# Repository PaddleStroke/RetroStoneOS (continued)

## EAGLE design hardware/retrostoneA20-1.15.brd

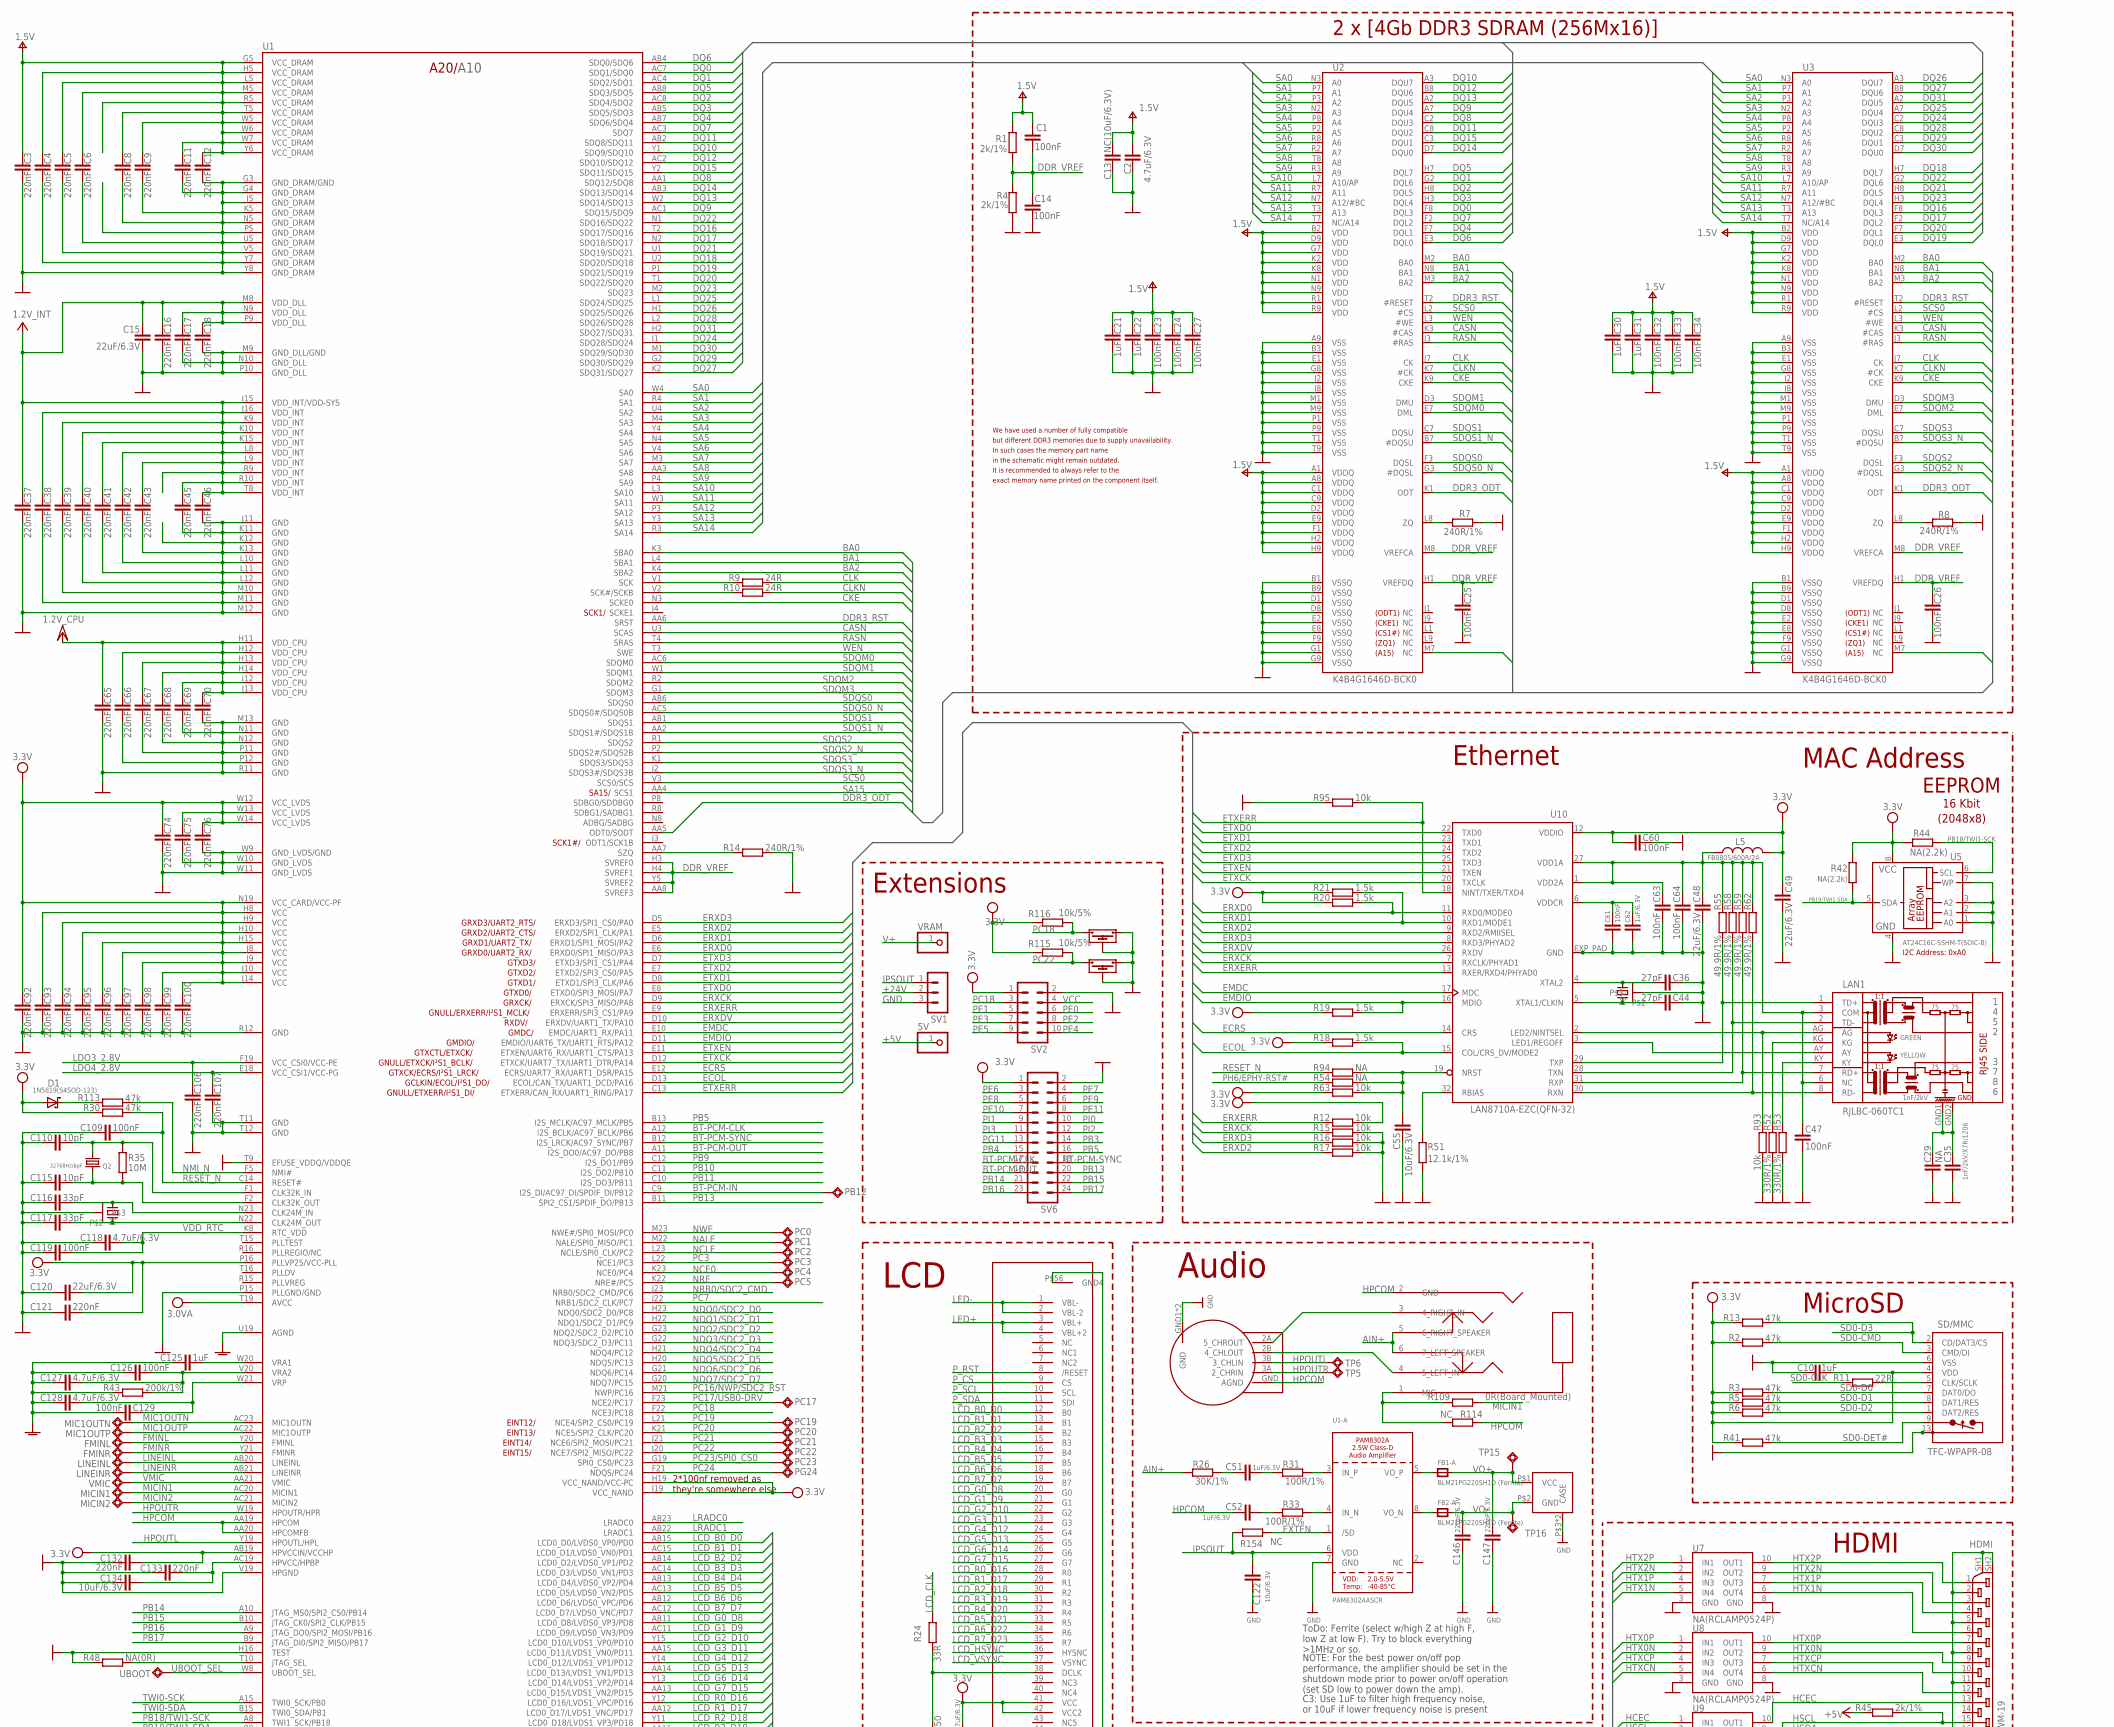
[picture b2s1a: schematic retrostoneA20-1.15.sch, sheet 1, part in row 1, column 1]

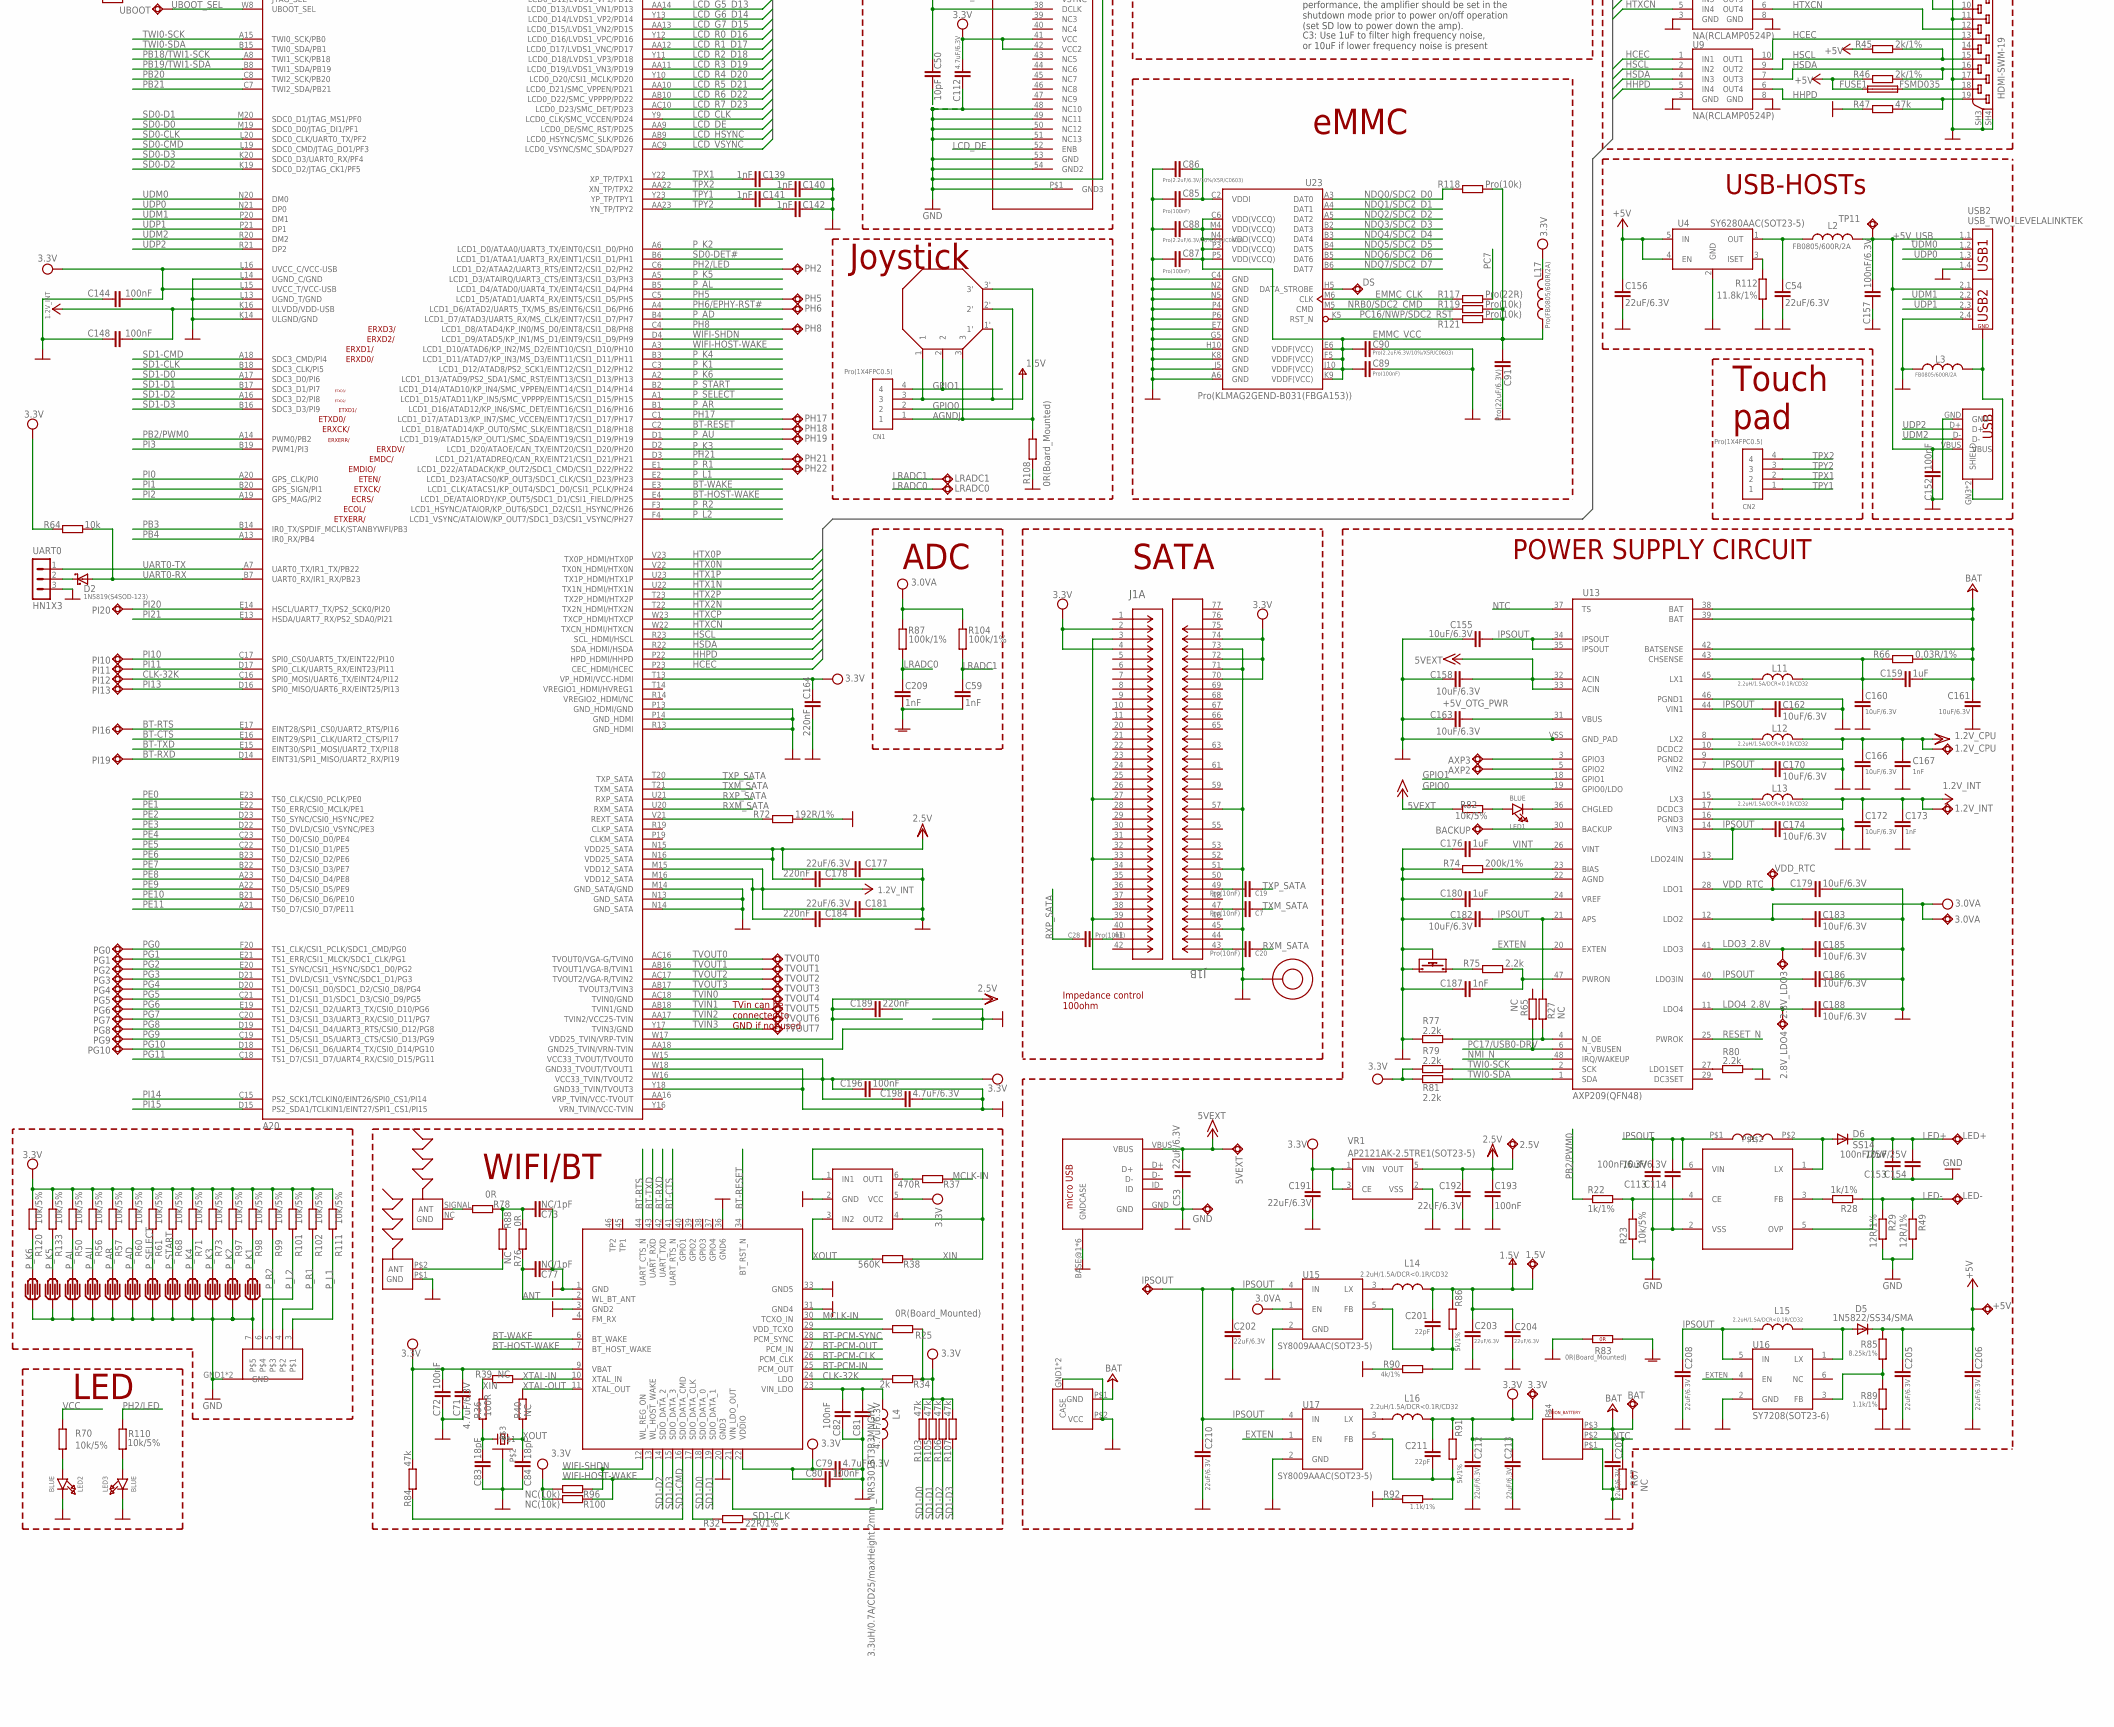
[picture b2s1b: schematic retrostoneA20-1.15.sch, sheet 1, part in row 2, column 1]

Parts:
1.2V_CPU, 1.2V_INT, 1.5V, 2.5V, 2.8V_LDO3, 2.8V_LDO4, 3.0VA, 3.3V, 5VEXT: TESTPADTESTPAD_40-ROUND; TESTPAD_40-ROUND
5V: PINHD-1X1; 1X01
+5V: TESTPADTESTPAD_40-ROUND; TESTPAD_40-ROUND
AXP2, AXP3: TESTPADTESTPAD30/30; TESTPAD_30-ROUND
BACKUP: TESTPADTESTPAD30/30; TESTPAD_30-ROUND
BAT: TESTPADTESTPAD_40-ROUND; TESTPAD_40-ROUND
C1, C14, C23, C24, C25, C26, C27, C32, C33, C34, C47, C60, C61, C63, C64, C72, C80, C82, C109, C119, C126, C129, C144, C148, C152, C193, C196: 100nF; C0402_TI
C2, C71, C79, C81, C112, C118, C127, C128, C198: 4.7uF/6.3V; C0603_DWS
C3, C4, C5, C6, C8, C9, C11, C12, C16, C17, C18, C37, C38, C39, C40, C41, C42, C43, C45, C46, C65, C66, C67, C68, C69, C70, C74, C75, C76, C92, C93, C94, C95, C96, C97, C98, C99, C100, C106, C107, C121, C132, C133, C164, C178, C184, C189: 220nF; C0402_TI
C7, C19, C20, C28: Pro(10nF); C0402_TI
C10, C21, C22, C30, C31, C125, C176, C180: 1uF; C0402_TI
C13: NC(10uF/6.3V); C0603_DWS
C15, C48, C49, C53, C54, C120, C156, C177, C181, C191, C192, C202, C203, C204, C205, C206, C207, C208, C210, C212, C213: 22uF/6.3V; C0603_DWS
C29: NA; C1206_5MILS_WS_ISO
C35: 1nF/2kV/X7R/1206; C1206_5MILS_WS_ISO
C36, C44: 27pF; C0402_TI
C50, C110, C115: 10pF; C0402_TI
C51, C52: 1uF/6.3V; C0402_TI
C55, C114, C122, C134, C155, C158, C160, C161, C162, C163, C166, C170, C172, C174, C179, C182, C183, C185, C186, C188: 10uF/6.3V; C0603_DWS
C59, C139, C140, C141, C142, C167, C173, C187, C209: 1nF; C0402_TI
C62: 1uF/6.3V; C0603_DWS
C73, C77: NC/1pF; C0402_TI
C83, C84: 18pF; C0402_TI
C85, C87, C89: Pro(100nF); C0402_TI
C86, C88, C90: Pro(2.2uF/6.3V/10%/X5R/C0603); C0603_DWS
C91: Pro(22uF/6.3V); C0603_DWS
C113, C157: 100nF/6.3V; C0402_TI
C116, C117: 33pF; C0402_TI
C146, C147: 220pF/6.3V; C0402_TI
C153: 100nF/25V; C0805_5MIL
C154: 10uF/25V; C0805_5MIL
C159: 1uF; C0603_DWS
C201, C211: 22pF; C0402_TI
CN1, CN2: Pro(1X4FPC0.5); FPC_0.5MM-4
D1, D2: 1N5819(S4SOD-123); SOD-123
D5: 1N5822/SS34/SMA; MELF-MLL41
D6: SS14; DO214AC
DOWN: PAD_BUTTON
DS: TESTPADTESTPAD_40-ROUND; TESTPAD_40-ROUND
FB1-A, FB2-A: BLM21PG220SH1D (Ferrite); _0805
FMINL: TESTPADTESTPAD_40-ROUND; TESTPAD_40-ROUND
FMINR: TESTPADTESTPAD_40-ROUND; TESTPAD_40-ROUND
FUSE1: FSMD035; 1206
GND: TESTPADTESTPAD_40-ROUND; TESTPAD_40-ROUND
HDMI: HDMI-SWM-19
IPSOUT: TESTPADTESTPAD_40-ROUND; TESTPAD_40-ROUND
J1: Pro(1-2199230-5-LITE); CONN67_2199230_LITE
K1, K2, K3, K4: PAD_BUTTON
L1: 22uH/CD32; CD32_INDUCTOR
L2, L3, L5: FB0805/600R/2A; L0805_5MIL_DWS
L4: 3.3uH/0.7A/CD25/maxHeight 2mm _NRS3015T3R3MNGHV; CD25
L11, L12, L13, L14, L15, L16: 2.2uH/1.5A/DCR<0.1R/CD32; CD32
L17: Pro(FB0805/600R/2A); L0805_5MIL_DWS
LAN1: RJLBC-060TC1; RJLBC-060TC1_MILLING
LED1, LED2, LED3: BLUE; CHIPLED_0805_NOOUTLINE
LED+: TESTPADTESTPAD_40-ROUND; TESTPAD_40-ROUND
LED-: TESTPADTESTPAD_40-ROUND; TESTPAD_40-ROUND
LEFT: PAD_BUTTON
LINEINL: TESTPADTESTPAD_40-ROUND; TESTPAD_40-ROUND
LINEINR: TESTPADTESTPAD_40-ROUND; TESTPAD_40-ROUND
LRADC0, LRADC1: TESTPADTESTPAD_40-ROUND; TESTPAD_40-ROUND
MIC1OUTN, MIC1OUTP: TESTPADTESTPAD_40-ROUND; TESTPAD_40-ROUND
MICIN1, MICIN2: TESTPADTESTPAD_40-ROUND; TESTPAD_40-ROUND
PB12: TESTPADTESTPAD_40-ROUND; TESTPAD_40-ROUND
PC0, PC1, PC2, PC3, PC4, PC5, PC17, PC19, PC20, PC21, PC22, PC23: TESTPADTESTPAD_40-ROUND; TESTPAD_40-ROUND
PG0, PG1, PG2, PG3, PG4, PG5, PG6, PG7, PG8, PG9, PG10, PG24: TESTPADTESTPAD_40-ROUND; TESTPAD_40-ROUND
PH2, PH5: TESTPADTESTPAD30/30; TESTPAD_30-ROUND
PH6, PH8, PH17, PH18, PH19, PH21, PH22: TESTPADTESTPAD_40-ROUND; TESTPAD_40-ROUND
PI10, PI11, PI12, PI13, PI16, PI19, PI20: TESTPADTESTPAD_40-ROUND; TESTPAD_40-ROUND
Q2: 32768Hz/6pF; MC-306
R1, R4, R45, R46: 2k/1%; R0402_TI
R2, R3, R5, R6, R13, R30, R41, R47, R84, R103, R105, R106, R107, R113: 47k; R0402_TI
R7, R8, R14: 240R/1%; R0402_TI
R9, R10: 24R; R0402_TI
R11: 22R; R0402_TI
R12, R15, R16, R17, R63, R64, R93, R95: 10k; R0402_TI
R18, R19, R20, R21: 1.5k; R0402_TI
R22, R28: 1k/1%; R0402_TI
R23, R50, R56, R57, R60, R61, R68, R70, R71, R73, R82, R97, R98, R99, R101, R102, R110, R111, R115, R116, R120, R133: 10k/5%; R0402_TI
R24: 33R; R0402_TI
R25, R108, R109: 0R(Board_Mounted); R0402_TI_0R
R26: 30K/1%; R0402_TI
R27, R39, R40, R65, R67, R88, R114, R154: NC; R0402_TI
R29, R49: 12R/1%; R0603_5MIL_DWS
R31, R33: 100R/1%; R0402_TI
R32: 22R/1%; R0402_TI
R34: 2k; R0402_TI
R35: 10M; R0402_TI
R36: 100R; R0402_TI
R37: 470R; R0402_TI
R38: 560K; R0402_TI
R42, R44: NA(2.2k); R0603_5MIL_DWS
R43, R74: 200k/1%; R0402_TI
R48: NA(0R); R0402_TI
R51: 12.1k/1%; R0402_TI
R52, R53: 330R/1%; R0603_5MIL_DWS
R54, R94: NA; R0402_TI
R55, R58, R59, R62: 49.9R/1%; R0402_TI
R66: 0.03R/1%; R1206_5MIL_WS
R72: 192R/1%; R0402_TI
R75, R77, R79, R80, R81: 2.2k; R0402_TI
R76, R78: 0R; R0402_TI
R83: 0R(Board_Mounted); 0603_0R
R85: 8.25k/1%; R0402_TI
R86, R91: 5k/1%; R0402_TI
R87, R104: 100k/1%; R0402_TI
R89, R92: 1.1k/1%; R0402_TI
R90: 4k/1%; R0402_TI
R96, R100: NC(10k); R0402_TI
R112: 11.8k/1%; R0402_TI
R117: Pro(22R); R0402_TI
R118, R119, R121: Pro(10k); R0402_TI
RIGHT: PAD_BUTTON
SD/MMC: TFC-WPAPR-08
SELECT, SELECT3, SELECT4: PAD_BUTTON
START: PAD_BUTTON
SV1: MA03-1
SV2: MA05-2
SV6: MA12-2
TP5, TP6, TP11, TP15, TP16: TESTPADTESTPAD_40-ROUND; TESTPAD_40-ROUND
TVOUT0, TVOUT2, TVOUT3: TESTPADTESTPAD_40-ROUND; TESTPAD_40-ROUND
TVOUT1, TVOUT4, TVOUT5, TVOUT6, TVOUT7: TESTPADTESTPAD30/30; TESTPAD_30-ROUND
U1: A20; TFBGA441
U1-A: PAM8302AASCR; MSOP8_0.65MM
U2, U3: K4B4G1646D-BCK0; FBGA96_SK
U4: SY6280AAC(SOT23-5); SOT23-5
U5: AT24C16C-SSHM-T(SOIC-8); SO-08MN
U7, U8, U9: NA(RCLAMP0524P); SLP2510P8
U10: LAN8710A-EZC(QFN-32); QFN-32(DRILLS)
U13: AXP209(QFN48); QFN48
U14: KA2707; SOT23-6
U15, U17: SY8009AAAC(SOT23-5); SOT23-5
U16: SY7208(SOT23-6); SOT23-6
U23: Pro(KLMAG2GEND-B031(FBGA153)); FBGA153
U$1: USB_HAYATO; USBA_HAYATO
U$2: AP6210; AP6212
U$3: 26MHZ_12pF; TSX-3225
U$4: JST_PH_VERT_5P
U$5, U$31, U$32: TACT_SWITCH_HORIZONTAL
U$6: NC(JST_PH_VERT_2P); JST_PH_VERT_2P
U$7: FPC_HAYATO
U$8: ESP8089_ANTSYM; ANT_ESP8206_SYM
U$15: JST2_HAYATO1.25_HOR_2PIN; JST1.25_HOR_2P
U$17: MICROUSB_HAYATO
U$18: BC-75-3PD700(750-800); BATTERY_CON_3PIN
U$20: SCREW_M2_04
U$21: 24MHz/20ppm/20pF; TSX-3225
U$23: 25MHZ/20pF/20ppm; TSX-3225
U$24: PJ342_5PIN; PJ342_6P
U$27: WHEEL_POT
U$29: NL27WZU04; SOT23-6
U$30: ANT_H2U262GKBA0100
U$33: JOYSTICK-POT
UART0: HN1X3
UBOOT: TESTPADTESTPAD_40-ROUND; TESTPAD_40-ROUND
UP: PAD_BUTTON
USB2: USB_TWO_LEVELALINKTEK; USB_TWO_LEVEL_ALINKTEK
VDD_RTC: TESTPADTESTPAD_40-ROUND; TESTPAD_40-ROUND
VMIC: TESTPADTESTPAD_40-ROUND; TESTPAD_40-ROUND
VR1: AP2121AK-2.5TRE1(SOT23-5); SOT-23-5
VRAM: PINHD-1X1; 1X01

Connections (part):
5VEXT: 5VEXT.1, C53.2, C158.2, R82.1, U13.32 (ACIN), U13.33 (ACIN), U$17.VBUS
+5V: 5V.1, +5V.1, C156.1, C205.1, C206.1, D5.1 (C), FUSE1.1, R45.2, R46.2, R85.2, U4.4 (EN), U4.5 (IN)
+5V_OTG_PWR: C163.2, U13.31 (VBUS)
+5V_USB: C152.1, C157.1, L2.1, TP11.1, U$1.VBUS, USB2.1.1, USB2.2.1
+24V: BAT.1, C159.2, C161.1, C207.2, R66.2, SV1.2, U13.38 (BAT), U13.39 (BAT), U13.42 (BATSENSE), U$6.P$1 (GND), U$18.P$3
AGNDJ: CN1.1, R108.1, U$33.3, U$33.3'
AIN+: R26.1, U$24.5 (6_RIGHT_SPEAKER), U$24.6 (7_LEFT_SPEAKER)
ANT: C77.2, R76.1, U$2.2 (WL_BT_ANT)
BA0: U1.K3 (SBA0), U2.M2 (BA0), U3.M2 (BA0)
BA1: U1.L4 (SBA1), U2.N8 (BA1), U3.N8 (BA1)
BA2: U1.K4 (SBA2), U2.M3 (BA2), U3.M3 (BA2)
BT-CTS: U1.E16 (EINT29/SPI1_CLK/UART2_CTS/PI17), U$2.41 (UART_RTS_N)
BT-HOST-WAKE: U1.E4 (LCD1_DE/ATAIORDY/KP_OUT5/SDC1_D1/CSI1_F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), U$2.7 (BT_HOST_WAKE)
BT-PCM-CLK: SV6.17, U1.A12 (I2S_BCLK/AC97_BCLK/PB6), U$2.26 (PCM_CLK)
BT-PCM-IN: PB12.1, U1.C9 (I2S_DI/AC97_DI/SPDIF_DI/PB12), U$2.25 (PCM_OUT)
BT-PCM-OUT: SV6.19, U1.A11 (I2S_DO0/AC97_DO/PB8), U$2.27 (PCM_IN)
BT-PCM-SYNC: SV6.18, U1.B12 (I2S_LRCK/AC97_SYNC/PB7), U$2.28 (PCM_SYNC)
BT-RESET: PH18.1, U1.C2 (LCD1_D18/ATAD14/KP_OUT0/SMC_SLK/EINT18/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), U$2.34 (BT_RST_N)
BT-RTS: PI16.1, U1.E17 (EINT28/SPI1_CS0/UART2_RTS/PI16), U$2.44 (UART_CTS_N)
BT-RXD: PI19.1, U1.D14 (EINT31/SPI1_MISO/UART2_RX/PI19), U$2.42 (UART_TXD)
BT-TXD: U1.E15 (EINT30/SPI1_MOSI/UART2_TX/PI18), U$2.43 (UART_RXD)
BT-WAKE: U1.E3 (LCD1_CLK/ATACS1/KP_OUT4/SDC1_D0/CSI1_PC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), U$2.6 (BT_WAKE)
CASN: U1.U3 (SCAS), U2.K3 (#CAS), U3.K3 (#CAS)
CHASSIS: C29.2, C35.2, LAN1.GND1, LAN1.GND2
CKE: U1.N3 (SCKE0), U2.K9 (CKE), U3.K9 (CKE)
CLK: R9.1, U2.J7 (CK), U3.J7 (CK)
CLK-32K: PI12.1, R34.1, U1.C16 (SPI0_MOSI/UART6_TX/EINT24/PI12), U$2.24 (LDO)
CLKN: R10.1, U2.K7 (#CK), U3.K7 (#CK)
DDR3_ODT: U1.AA5 (ODT0/SODT), U2.K1 (ODT), U3.K1 (ODT)
DDR3_RST: U1.AA6 (SRST), U2.T2 (#RESET), U3.T2 (#RESET)
DDR_VREF: C1.2, C14.2, C25.2, C26.2, R1.1, R4.2, U1.AA8 (SVREF3), U1.H3 (SVREF0), U1.H4 (SVREF1), U1.Y5 (SVREF2), U2.H1 (VREFDQ), U2.M8 (VREFCA), U3.H1 (VREFDQ), U3.M8 (VREFCA)
DQ0: U1.AC7 (SDQ1/SDQ0), U2.F8 (DQL3)
DQ1: U1.AC4 (SDQ2/SDQ1), U2.G2 (DQL6)
DQ2: U1.AC8 (SDQ4/SDQ2), U2.H8 (DQL5)
DQ3: U1.AB5 (SDQ5/SDQ3), U2.H3 (DQL4)
DQ4: U1.AB7 (SDQ6/SDQ4), U2.F7 (DQL1)
DQ5: U1.AB8 (SDQ3/SDQ5), U2.H7 (DQL7)
DQ6: U1.AB4 (SDQ0/SDQ6), U2.E3 (DQL0)
DQ7: U1.AC3 (SDQ7), U2.F2 (DQL2)
DQ8: U1.AA1 (SDQ12/SDQ8), U2.C2 (DQU3)
DQ9: U1.AC1 (SDQ15/SDQ9), U2.A7 (DQU4)
DQ10: U1.Y1 (SDQ9/SDQ10), U2.A3 (DQU7)
DQ11: U1.AB2 (SDQ8/SDQ11), U2.C8 (DQU2)
DQ12: U1.AC2 (SDQ10/SDQ12), U2.B8 (DQU6)
DQ13: U1.W2 (SDQ14/SDQ13), U2.A2 (DQU5)
DQ14: U1.AB3 (SDQ13/SDQ14), U2.D7 (DQU0)
DQ15: U1.Y2 (SDQ11/SDQ15), U2.C3 (DQU1)
DQ16: U1.T2 (SDQ17/SDQ16), U3.F8 (DQL3)
DQ17: U1.N2 (SDQ18/SDQ17), U3.F2 (DQL2)
DQ18: U1.U2 (SDQ20/SDQ18), U3.H7 (DQL7)
DQ19: U1.P1 (SDQ21/SDQ19), U3.E3 (DQL0)
DQ20: U1.T1 (SDQ22/SDQ20), U3.F7 (DQL1)
DQ21: U1.U1 (SDQ19/SDQ21), U3.H8 (DQL5)
DQ22: U1.N1 (SDQ16/SDQ22), U3.G2 (DQL6)
DQ23: U1.M2 (SDQ23), U3.H3 (DQL4)
DQ24: U1.J1 (SDQ28/SDQ24), U3.C2 (DQU3)
DQ25: U1.L1 (SDQ24/SDQ25), U3.A7 (DQU4)
DQ26: U1.H1 (SDQ25/SDQ26), U3.A3 (DQU7)
DQ27: U1.K2 (SDQ31/SDQ27), U3.B8 (DQU6)
DQ28: U1.L2 (SDQ26/SDQ28), U3.C8 (DQU2)
DQ29: U1.G2 (SDQ30/SDQ29), U3.C3 (DQU1)
DQ30: U1.M1 (SDQ29/SQD30), U3.D7 (DQU0)
DQ31: U1.H2 (SDQ27/SDQ31), U3.A2 (DQU5)
ECOL: R18.2, U1.D13 (ECOL/CAN_TX/UART1_DCD/PA16), U10.15 (COL/CRS_DV/MODE2)
ECRS: U1.E12 (ECRS/UART7_RX/UART1_DSR/PA15), U10.14 (CRS)
EMDC: U1.E10 (EMDC/UART1_RX/PA11), U10.17 (MDC)
EMDIO: R19.2, U1.D11 (EMDIO/UART6_TX/UART1_RTS/PA12), U10.16 (MDIO)
EMMC_CLK: R117.2, U23.M6 (CLK)
EMMC_VCC: C87.1, C88.2, C89.1, C90.2, C91.1, L17.2, R118.1, R119.1, R121.1, U23.C6 (VDD(VCCQ)), U23.E6 (VDDF(VCC)), U23.F5 (VDDF(VCC)), U23.J10 (VDDF(VCC)), U23.K9 (VDDF(VCC)), U23.M4 (VDD(VCCQ)), U23.N4 (VDD(VCCQ)), U23.P3 (VDD(VCCQ)), U23.P5 (VDD(VCCQ))
ERXCK: R15.1, U1.D9 (ERXCK/SPI3_MISO/PA8), U10.7 (RXCLK/PHYAD1)
ERXD0: R20.2, U1.E6 (ERXD0/SPI1_MISO/PA3), U10.11 (RXD0/MODE0)
ERXD1: R21.2, U1.D6 (ERXD1/SPI1_MOSI/PA2), U10.10 (RXD1/MODE1)
ERXD2: R17.1, U1.E5 (ERXD2/SPI1_CLK/PA1), U10.9 (RXD2/RMIISEL)
ERXD3: R16.1, U1.D5 (ERXD3/SPI1_CS0/PA0), U10.8 (RXD3/PHYAD2)
ERXDV: U1.D10 (ERXDV/UART1_TX/PA10), U10.26 (RXDV)
ERXERR: R12.1, U1.E9 (ERXERR/SPI3_CS1/PA9), U10.13 (RXER/RXD4/PHYAD0)
ETHERNET_VDD: C47.2, C48.2, C63.2, C64.2, L5.1, LAN1.3 (COM), LAN1.6 (NC), R55.2, R58.2, R59.2, R62.2, U10.1 (VDD2A), U10.27 (VDD1A)
ETXCK: U1.D12 (ETXCK/UART7_TX/UART1_DTR/PA14), U10.20 (TXCLK)
ETXD0: U1.E8 (ETXD0/SPI3_MOSI/PA7), U10.22 (TXD0)
ETXD1: U1.D8 (ETXD1/SPI3_CLK/PA6), U10.23 (TXD1)
ETXD2: U1.E7 (ETXD2/SPI3_CS0/PA5), U10.24 (TXD2)
ETXD3: U1.D7 (ETXD3/SPI1_CS1/PA4), U10.25 (TXD3)
ETXEN: U1.E11 (ETXEN/UART6_RX/UART1_CTS/PA13), U10.21 (TXEN)
ETXERR: R95.2, U1.C13 (ETXERR/CAN_RX/UART1_RING/PA17), U10.18 (NINT/TXER/TXD4)
EXTEN: R154.2, U1-A.1 (/SD), U13.20 (EXTEN), U16.4 (EN), U17.1 (EN)
FMINL: FMINL.1, U1.Y20 (FMINL)
FMINR: FMINR.1, U1.Y21 (FMINR)
GND: C2.1, C3.1, C4.1, C5.1, C6.1, C8.1, C9.1, C10.2, C11.1, C12.1, C13.1, C14.1, C15.1, C16.1, C17.1, C18.1, C21.1, C22.1, C23.1, C24.1, C25.1, C26.1, C27.1, C29.1, C30.1, C31.1, C32.1, C33.1, C34.1, C35.1, C36.1, C37.1, C38.1, C39.1, C40.1, C41.1, C42.1, C43.1, C44.1, C45.1, C46.1, C47.1, C48.1, C49.1, C50.2, C53.1, C54.2, C55.1, C60.1, C61.1, C62.1, C63.1, C64.1, C65.1, C66.1, C67.1, C68.1, C69.1, C70.1, C71.2, C72.1, C73.1, C74.1, C75.1, C76.1, C77.1, C79.1, C80.2, C81.2, C82.1, C83.1, C84.1, C85.2, C86.1, C87.2, C88.1, C89.2, C90.1, C91.2, C92.1, C93.1, C94.1, C95.1, C96.1, C97.1, C98.1, C99.1, C100.1, C106.1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
GNDA: C59.2, C125.1, C126.1, C127.1, C128.1, C129.1, C209.2, R43.2, R83.2 (1.2), U1.U19 (AGND)
GPIO0: CN1.2, U13.19 (GPIO0/LDO), U$33.2'
GPIO1: CN1.4, U13.18 (GPIO1), U$33.2
HCEC: HDMI.13, U1.P23 (CEC_HDMI/HCEC), U9.1 (IN1), U9.10 (OUT1)
HDMI_5V_SOURCE: FUSE1.2, HDMI.18
HHPD: HDMI.19, R47.1, U1.P22 (HPD_HDMI/HHPD), U9.5 (IN4), U9.6 (OUT4)
HPCOM: C52.1, R114.1, U1.AA19 (HPCOM), U1.AA20 (HPCOMFB), U$24.2 (GND), U$27.GND (AGND)
HPOUTL: TP6.1, U1.Y19 (HPOUTL/HPL), U$27.3B (3_CHLIN)
HPOUTR: TP5.1, U1.W19 (HPOUTR/HPR), U$27.3A (2_CHRIN)
HSCL: HDMI.15, R45.1, U1.R23 (SCL_HDMI/HSCL), U9.2 (IN2), U9.9 (OUT2)
HSDA: HDMI.16, R46.1, U1.R22 (SDA_HDMI/HSDA), U9.4 (IN3), U9.7 (OUT3)
HTX0N: HDMI.9, U1.V22 (TX0N_HDMI/HTX0N), U8.2 (IN2), U8.9 (OUT2)
HTX0P: HDMI.7, U1.V23 (TX0P_HDMI/HTX0P), U8.1 (IN1), U8.10 (OUT1)
HTX1N: HDMI.6, U1.U22 (TX1N_HDMI/HTX1N), U7.5 (IN4), U7.6 (OUT4)
HTX1P: HDMI.4, U1.U23 (TX1P_HDMI/HTX1P), U7.4 (IN3), U7.7 (OUT3)
HTX2N: HDMI.3, U1.T22 (TX2N_HDMI/HTX2N), U7.2 (IN2), U7.9 (OUT2)
HTX2P: HDMI.1, U1.T23 (TX2P_HDMI/HTX2P), U7.1 (IN1), U7.10 (OUT1)
HTXCN: HDMI.12, U1.W22 (TXCN_HDMI/HTXCN), U8.5 (IN4), U8.6 (OUT4)
HTXCP: HDMI.10, U1.W23 (TXCP_HDMI/HTXCP), U8.4 (IN3), U8.7 (OUT3)
IPSOUT: C113.2, C114.2, C122.2, C155.2, C162.1, C170.1, C174.1, C182.2, C186.1, C202.1, C208.2, C210.1, IPSOUT.1, L1.P$1, L15.1, R27.1, R154.1, SV1.1, U1-A.6 (VDD), U13.7 (VIN2), U13.13 (LDO24IN), U13.14 (VIN3), U13.21 (APS), U13.34 (IPSOUT), U13.35 (IPSOUT), U13.40 (LDO3IN), U13.44 (VIN1), U14.6 (VIN), U15.4 (IN), U16.5 (IN), U17.4 (IN)
LCD_B0_D0: U1.AB15 (LCD0_D0/LVDS0_VP0/PD0), U$7.12 (B0)
LCD_B1_D1: U1.AC15 (LCD0_D1/LVDS0_VN0/PD1), U$7.13 (B1)
LCD_B2_D2: U1.AB14 (LCD0_D2/LVDS0_VP1/PD2), U$7.14 (B2)
LCD_B3_D3: U1.AC14 (LCD0_D3/LVDS0_VN1/PD3), U$7.15 (B3)
LCD_B4_D4: U1.AB13 (LCD0_D4/LVDS0_VP2/PD4), U$7.16 (B4)
LCD_B5_D5: U1.AC13 (LCD0_D5/LVDS0_VN2/PD5), U$7.17 (B5)
LCD_B6_D6: U1.AB12 (LCD0_D6/LVDS0_VPC/PD6), U$7.18 (B6)
LCD_B7_D7: U1.AC12 (LCD0_D7/LVDS0_VNC/PD7), U$7.19 (B7)
LCD_CLK: R24.2, U1.Y9 (LCD0_CLK/SMC_VCCEN/PD24)
LCD_DE: U1.AA9 (LCD0_DE/SMC_RST/PD25), U$7.52 (ENB)
LCD_G0_D8: U1.AB11 (LCD0_D8/LVDS0_VP3/PD8), U$7.20 (G0)
LCD_G1_D9: U1.AC11 (LCD0_D9/LVDS0_VN3/PD9), U$7.21 (G1)
LCD_G2_D10: U1.Y15 (LCD0_D10/LVDS1_VP0/PD10), U$7.22 (G2)
LCD_G3_D11: U1.AA15 (LCD0_D11/LVDS1_VN0/PD11), U$7.23 (G3)
LCD_G4_D12: U1.Y14 (LCD0_D12/LVDS1_VP1/PD12), U$7.24 (G4)
LCD_G5_D13: U1.AA14 (LCD0_D13/LVDS1_VN1/PD13), U$7.25 (G5)
LCD_G6_D14: U1.Y13 (LCD0_D14/LVDS1_VP2/PD14), U$7.26 (G6)
LCD_G7_D15: U1.AA13 (LCD0_D15/LVDS1_VN2/PD15), U$7.27 (G7)
LCD_HSYNC: U1.AB9 (LCD0_HSYNC/SMC_SLK/PD26), U$7.36 (HYSNC)
LCD_R0_D16: U1.Y12 (LCD0_D16/LVDS1_VPC/PD16), U$7.28 (R0)
LCD_R1_D17: U1.AA12 (LCD0_D17/LVDS1_VNC/PD17), U$7.29 (R1)
LCD_R2_D18: U1.Y11 (LCD0_D18/LVDS1_VP3/PD18), U$7.30 (R2)
LCD_R3_D19: U1.AA11 (LCD0_D19/LVDS1_VN3/PD19), U$7.31 (R3)
LCD_R4_D20: U1.Y10 (LCD0_D20/CSI1_MCLK/PD20), U$7.32 (R4)
LCD_R5_D21: U1.AA10 (LCD0_D21/SMC_VPPEN/PD21), U$7.33 (R5)
LCD_R6_D22: U1.AB10 (LCD0_D22/SMC_VPPPP/PD22), U$7.34 (R6)
LCD_R7_D23: U1.AC10 (LCD0_D23/SMC_DET/PD23), U$7.35 (R7)
LCD_VSYNC: U1.AC9 (LCD0_VSYNC/SMC_SDA/PD27), U$7.37 (VSYNC)
LDO3_2.8V: 2.8V_LDO3.1, C106.2, C185.1, U1.F19 (VCC_CSI0/VCC-PE), U13.41 (LDO3)
LDO4_2.8V: 2.8V_LDO4.1, C107.2, C188.1, U1.E18 (VCC_CSI1/VCC-PG), U13.11 (LDO4)
LED+: C153.2, C154.2, D6.C, LED+.1, U14.5 (OVP), U$7.3 (VBL+), U$7.4 (VBL+2)
LED-: LED-.1, R28.1, R29.1, R49.1, U$7.1 (VBL-), U$7.2 (VBL-2)
LINEINL: LINEINL.1, U1.AB20 (LINEINL)
LINEINR: LINEINR.1, U1.AB21 (LINEINR)
LR: U$24.3 (4_RIGHT_IN), U$27.2A (5_CHROUT)
LRADC0: C209.1, LRADC0.1, R87.2, U1.AB23 (LRADC0)
LRADC1: C59.1, LRADC1.1, R104.2, U1.AB22 (LRADC1)
MCLK-IN: R37.2, U$2.30 (TCXO_IN)
MIC1OUTN: MIC1OUTN.1, U1.AC23 (MIC1OUTN)
MIC1OUTP: MIC1OUTP.1, U1.AC22 (MIC1OUTP)
MICIN1: MICIN1.1, R109.2, U1.AC20 (MICIN1)
MICIN2: MICIN2.1, U1.AC21 (MICIN2)
unnamed: C133.2, C134.2, U1.AC19 (HPVCC/HPBP)
unnamed: R14.2, U1.AA7 (SZQ)
unnamed: R7.2, U2.L8 (ZQ)
unnamed: LED2.A, R70.2
unnamed: R22.2, R23.2, U14.4 (CE)
unnamed: D6.A, L1.P$2, U14.1 (LX)
unnamed: D2.C, UART0.2
unnamed: L14.1, U15.3 (LX)
unnamed: R109.1, R114.2, U$24.1 (MIC)
unnamed: D1.C, R113.2
unnamed: LED1.C, U13.36 (CHGLED)
unnamed: R80.1, U13.27 (LDO1SET)
unnamed: C83.2, R36.2, U$3.P$1
unnamed: C110.2, Q2.4 (2), R35.1, U1.F1 (CLK32K_IN)
unnamed: R8.2, U3.L8 (ZQ)
unnamed: C50.1, R24.1, U$7.38 (DCLK)
unnamed: R28.2, U14.3 (FB)
unnamed: R112.2, U4.3 (ISET)
unnamed: C201.2, R86.2, R90.1, U15.5 (FB)
unnamed: C28.2, J1.41
unnamed: R75.1, U$5.P$2
unnamed: C20.2, J1.43
unnamed: R32.1, U$2.17 (SDIO_DATA_CLK)
unnamed: C54.1, L2.2, U4.1 (OUT)
unnamed: C7.2, J1.47
unnamed: C19.2, J1.49
unnamed: C73.2, R76.2, R78.1, R88.1
unnamed: L4.2, U$2.21 (VIN_LDO_OUT)
unnamed: C81.1, C82.2, L4.1, U$2.23 (VIN_LDO)
unnamed: BACKUP.1, U13.30 (BACKUP)
unnamed: R37.1, U$29.6 (OUT1)
unnamed: R88.2, U$8.P$2 (ANT)
unnamed: R78.2, U$30.SIGNAL (ANT)
unnamed: AXP2.1, U13.5 (GPIO2)
unnamed: DS.1, U23.H5 (DATA_STROBE)
unnamed: AXP3.1, U13.3 (GPIO3)
unnamed: R25.1, U$2.29 (VDD_TCXO)
unnamed: LED1.A, R82.2
unnamed: LED3.A, R110.2
unnamed: C51.1, R26.2
unnamed: L16.1, U17.3 (LX)
unnamed: C211.2, R91.2, R92.1, U17.5 (FB)
unnamed: R33.2, U1-A.4 (IN_N)
unnamed: R31.2, U1-A.3 (IN_P)
unnamed: C52.2, R33.1
unnamed: FB2-A.1, U1-A.8 (VO_N)
unnamed: FB1-A.1, U1-A.5 (VO_P)
unnamed: C51.2, R31.1
unnamed: U$24.4 (5_LEFT_IN), U$27.2B (4_CHLOUT)
unnamed: LAN1.1 (TD+), R55.1, U10.29 (TXP)
unnamed: LAN1.2 (TD-), R58.1, U10.28 (TXN)
unnamed: LAN1.7 (RD+), R59.1, U10.31 (RXP)
unnamed: LAN1.8 (RD-), R62.1, U10.30 (RXN)
unnamed: LAN1.AY, U10.3 (LED1/REGOFF)
unnamed: LAN1.AG, R93.1, U10.2 (LED2/NINTSEL)
unnamed: LAN1.KY, R53.1
unnamed: R51.2, U10.32 (RBIAS)
unnamed: C61.2, C62.2, U10.6 (VDDCR)
unnamed: LAN1.KG, R52.1
unnamed: C115.2, Q2.1, R35.2, U1.F2 (CLK32K_OUT)
unnamed: R72.2, U1.V21 (REXT_SATA)
unnamed: R74.2, U13.23 (BIAS)
unnamed: C128.2, C129.2, U1.W21 (VRP)
unnamed: D5.2 (A), L15.2, U16.1 (LX)
unnamed: R85.1, R89.1, U16.3 (FB)
unnamed: L11.1, U13.45 (LX1)
unnamed: C159.1, C160.1, L11.2, R66.1, U13.43 (CHSENSE)
unnamed: L12.1, U13.8 (LX2)
unnamed: L13.1, U13.15 (LX3)
unnamed: C180.2, U13.24 (VREF)
unnamed: C125.2, U1.W20 (VRA1)
unnamed: C187.2, R75.2, U13.47 (PWRON)
unnamed: R27.2, R77.2, U13.4 (N_OE)
unnamed: C126.2, C127.2, R43.1, U1.V20 (VRA2)
unnamed: R48.1, U1.T10 (JTAG_SEL)
unnamed: L3.2, U$1.GN3 (SHIELD), U$1.GND2 (SHIELD), USB2.GND1, USB2.GND2 (GND1), USB2.GND3 (GND1), USB2.GND4 (GND1)
NALE: PC1.1, U1.M22 (NALE/SPI0_MISO/PC1)
NCE0: PC4.1, U1.K23 (NCE0/PC4)
NCLE: PC2.1, U1.L23 (NCLE/SPI0_CLK/PC2)
NDQ0/SDC2_D0: R118.2, U1.H23 (NDQ0/SDC2_D0/PC8), U23.A3 (DAT0)
NDQ1/SDC2_D1: U1.H22 (NDQ1/SDC2_D1/PC9), U23.A4 (DAT1)
NDQ2/SDC2_D2: U1.G23 (NDQ2/SDC2_D2/PC10), U23.A5 (DAT2)
NDQ3/SDC2_D3: U1.G22 (NDQ3/SDC2_D3/PC11), U23.B2 (DAT3)
NDQ4/SDC2_D4: U1.H21 (NDQ4/PC12), U23.B3 (DAT4)
NDQ5/SDC2_D5: U1.H20 (NDQ5/PC13), U23.B4 (DAT5)
NDQ6/SDC2_D6: U1.G21 (NDQ6/PC14), U23.B5 (DAT6)
NDQ7/SDC2_D7: U1.G20 (NDQ7/PC15), U23.B6 (DAT7)
NMI_N: R113.1, U1.F5 (NMI#), U13.48 (IRQ/WAKEUP)
NRB0/SDC2_CMD: R119.2, U1.J23 (NRB0/SDC2_CMD/PC6), U23.M5 (CMD)
NRE: PC5.1, U1.K22 (NRE#/PC5)
NRST: C55.2, R54.2, R63.2, R94.2, U10.19 (NRST)
NTC: R67.1, U13.37 (TS), U$18.P$2
NWE: PC0.1, U1.M23 (NWE#/SPI0_MOSI/PC0)
PB2/PWM0: R22.1, U1.A14 (PWM0/PB2)
PB3: SV6.14, U1.B14 (IR0_TX/SPDIF_MCLK/STANBYWFI/PB3)
PB4: SV6.15, U1.A13 (IR0_RX/PB4)
PB5: SV6.16, U1.B13 (I2S_MCLK/AC97_MCLK/PB5)
PB9: U1.C12 (I2S_DO1/PB9)
PB10: U1.C11 (I2S_DO2/PB10)
PB11: U1.C10 (I2S_DO3/PB11)
PB13: SV6.20, U1.B11 (SPI2_CS1/SPDIF_DO/PB13)
PB14: SV6.21, U1.A10 (JTAG_MS0/SPI2_CS0/PB14)
PB15: SV6.22, U1.B10 (JTAG_CK0/SPI2_CLK/PB15)
PB16: SV6.23, U1.A9 (JTAG_DO0/SPI2_MOSI/PB16)
PB17: SV6.24, U1.B9 (JTAG_DI0/SPI2_MISO/PB17)
PB18/TWI1-SCK: R44.2, U1.A8 (TWI1_SCK/PB18), U5.6 (SCL)
PB19/TWI1-SDA: R42.1, U1.B8 (TWI1_SDA/PB19), U5.5 (SDA)
PB20: U1.C8 (TWI2_SCK/PB20)
PB21: U1.C7 (TWI2_SDA/PB21)
PC3: PC3.1, U1.L22 (NCE1/PC3)
PC7: R117.1, U1.J22 (NRB1/SDC2_CLK/PC7)
PC16/NWP/SDC2_RST: R121.2, U1.M21 (NWP/PC16), U23.K5 (RST_N)
PC17/USB0-DRV: PC17.1, R65.2, U1.F23 (NCE2/PC17), U13.6 (N_VBUSEN)
PC18: R116.2, SV2.3, U1.F22 (NCE3/PC18), U$32.P$3
PC19: PC19.1, U1.L21 (NCE4/SPI2_CS0/PC19)
PC20: PC20.1, U1.K21 (NCE5/SPI2_CLK/PC20)
PC21: PC21.1, U1.J21 (NCE6/SPI2_MOSI/PC21)
PC22: PC22.1, R115.2, U1.J20 (NCE7/SPI2_MISO/PC22), U$31.P$3
PC23/SPI0_CS0: PC23.1, U1.G19 (SPI0_CS0/PC23)
PC24: PG24.1, U1.F21 (NDQS/PC24)
PE0: SV2.6, U1.E23 (TS0_CLK/CSI0_PCLK/PE0)
PE1: SV2.5, U1.E22 (TS0_ERR/CSI0_MCLK/PE1)
PE2: SV2.8, U1.D23 (TS0_SYNC/CSI0_HSYNC/PE2)
PE3: SV2.7, U1.D22 (TS0_DVLD/CSI0_VSYNC/PE3)
PE4: SV2.10, U1.C23 (TS0_D0/CSI0_D0/PE4)
PE5: SV2.9, U1.C22 (TS0_D1/CSI0_D1/PE5)
PE6: SV6.3, U1.B23 (TS0_D2/CSI0_D2/PE6)
PE7: SV6.4, U1.B22 (TS0_D3/CSI0_D3/PE7)
PE8: SV6.5, U1.A23 (TS0_D4/CSI0_D4/PE8)
PE9: SV6.6, U1.A22 (TS0_D5/CSI0_D5/PE9)
PE10: SV6.7, U1.B21 (TS0_D6/CSI0_D6/PE10)
PE11: SV6.8, U1.A21 (TS0_D7/CSI0_D7/PE11)
PG0: PG0.1, U1.F20 (TS1_CLK/CSI1_PCLK/SDC1_CMD/PG0)
PG1: PG1.1, U1.E21 (TS1_ERR/CSI1_MLCK/SDC1_CLK/PG1)
PG2: PG2.1, U1.E20 (TS1_SYNC/CSI1_HSYNC/SDC1_D0/PG2)
PG3: PG3.1, U1.D21 (TS1_DVLD/CSI1_VSYNC/SDC1_D1/PG3)
PG4: PG4.1, U1.D20 (TS1_D0/CSI1_D0/SDC1_D2/CSI0_D8/PG4)
PG5: PG5.1, U1.C21 (TS1_D1/CSI1_D1/SDC1_D3/CSI0_D9/PG5)
PG6: PG6.1, U1.E19 (TS1_D2/CSI1_D2/UART3_TX/CSI0_D10/PG6)
PG7: PG7.1, U1.C20 (TS1_D3/CSI1_D3/UART3_RX/CSI0_D11/PG7)
PG8: PG8.1, U1.D19 (TS1_D4/CSI1_D4/UART3_RTS/CSI0_D12/PG8)
PG9: PG9.1, U1.C19 (TS1_D5/CSI1_D5/UART3_CTS/CSI0_D13/PG9)
PG10: PG10.1, U1.D18 (TS1_D6/CSI1_D6/UART4_TX/CSI0_D14/PG10)
PG11: SV6.13, U1.C18 (TS1_D7/CSI1_D7/UART4_RX/CSI0_D15/PG11)
PH2/LED: PH2.1, R110.1, U1.C6 (LCD1_D2/ATAA2/UART3_RTS/EINT2/CSI1_D2/P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)
PH5: PH5.1, U1.C5 (LCD1_D5/ATAD1/UART4_RX/EINT5/CSI1_D5/PH5)
PH6/EPHY-RST#: PH6.1, R54.1, U1.A4 (LCD1_D6/ATAD2/UART5_TX/MS_BS/EINT6/CSI1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)
PH8: PH8.1, U1.C4 (LCD1_D8/ATAD4/KP_IN0/MS_D0/EINT8/CSI1_D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)
PH17: PH17.1, U1.C1 (LCD1_D17/ATAD13/KP_IN7/SMC_VCCEN/EINT17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)
PH21: PH21.1, U1.D3 (LCD1_D21/ATADREQ/CAN_RX/EINT21/CSI1_D21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)
PI0: SV6.10, U1.A20 (GPS_CLK/PI0)
PI1: SV6.9, U1.B20 (GPS_SIGN/PI1)
PI2: SV6.12, U1.A19 (GPS_MAG/PI2)
PI3: SV6.11, U1.B19 (PWM1/PI3)
PI10: PI10.1, U1.C17 (SPI0_CS0/UART5_TX/EINT22/PI10)
PI11: PI11.1, U1.D17 (SPI0_CLK/UART5_RX/EINT23/PI11)
PI13: PI13.1, U1.D16 (SPI0_MISO/UART6_RX/EINT25/PI13)
PI14: U1.C15 (PS2_SCK1/TCLKIN0/EINT26/SPI0_CS1/PI14)
PI15: U1.D15 (PS2_SDA1/TCLKIN1/EINT27/SPI1_CS1/PI15)
PI20: PI20.1, U1.E14 (HSCL/UART7_TX/PS2_SCK0/PI20)
PI21: U1.E13 (HSDA/UART7_RX/PS2_SDA0/PI21)
P_AD: DOWN.P$1 (GND), R60.2, U1.B4 (LCD1_D7/ATAD3/UART5_RX/MS_CLK/EINT7/CSI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)
P_AL: LEFT.P$1 (GND), R50.2, U1.B5 (LCD1_D4/ATAD0/UART4_TX/EINT4/CSI1_D4/PH4)
P_AR: R57.2, RIGHT.P$1 (GND), U1.B1 (LCD1_D16/ATAD12/KP_IN6/SMC_DET/EINT16/C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)
P_AU: PH19.1, R56.2, U1.D1 (LCD1_D19/ATAD15/KP_OUT1/SMC_SDA/EINT19/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), UP.P$1 (GND)
P_CS: U$7.9 (CS)
P_K1: K1.P$1 (GND), R98.2, U1.C3 (LCD1_D12/ATAD8/PS2_SCK1/EINT12/CSI1_D12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)
P_K2: K2.P$1 (GND), R97.2, U1.A6 (LCD1_D0/ATAA0/UART3_TX/EINT0/CSI1_D0/PH0)
P_K3: K3.P$1 (GND), R73.2, U1.D2 (LCD1_D20/ATAOE/CAN_TX/EINT20/CSI1_D20/P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)
P_K4: K4.P$1 (GND), R71.2, U1.B3 (LCD1_D11/ATAD7/KP_IN3/MS_D3/EINT11/CSI1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)
P_K5: R133.2, SELECT3.P$1 (GND), U1.A5 (LCD1_D3/ATAIRQ/UART3_CTS/EINT3/CSI1_D3/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)
P_K6: R120.2, SELECT4.P$1 (GND), U1.A2 (LCD1_D13/ATAD9/PS2_SDA1/SMC_RST/EINT13/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)
P_L1: R111.2, U1.E2 (LCD1_D23/ATACS0/KP_OUT3/SDC1_CLK/CSI1_D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), U$4.3
P_L2: R101.2, U1.F4 (LCD1_VSYNC/ATAIOW/KP_OUT7/SDC1_D3/CSI1_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), U$4.6
P_R1: PH22.1, R102.2, U1.E1 (LCD1_D22/ATADACK/KP_OUT2/SDC1_CMD/CSI1_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), U$4.4
P_R2: R99.2, U1.F3 (LCD1_HSYNC/ATAIOR/KP_OUT6/SDC1_D2/CSI1_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), U$4.5
P_RST: U$7.8 (/RESET)
P_SCL: U$7.10 (SCL)
P_SDA: U$7.11 (SDI)
P_SELECT: R61.2, SELECT.P$1 (GND), U1.A1 (LCD1_D15/ATAD11/KP_IN5/SMC_VPPPP/EINT15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)
P_START: R68.2, START.P$1 (GND), U1.B2 (LCD1_D14/ATAD10/KP_IN4/SMC_VPPEN/EINT14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)
RASN: U1.T4 (SRAS), U2.J3 (#RAS), U3.J3 (#RAS)
RESET_N: C109.2, R30.1, R94.1, U1.C14 (RESET#), U13.25 (PWROK)
RXM_SATA: C20.1, U1.U20 (RXM_SATA)
RXP_SATA: C28.1, U1.U21 (RXP_SATA)
SA0: U1.W4 (SA0), U2.N3 (A0), U3.N3 (A0)
SA1: U1.R4 (SA1), U2.P7 (A1), U3.P7 (A1)
SA2: U1.U4 (SA2), U2.P3 (A2), U3.P3 (A2)
SA3: U1.M4 (SA3), U2.N2 (A3), U3.N2 (A3)
SA4: U1.Y4 (SA4), U2.P8 (A4), U3.P8 (A4)
SA5: U1.N4 (SA5), U2.P2 (A5), U3.P2 (A5)
SA6: U1.V4 (SA6), U2.R8 (A6), U3.R8 (A6)
SA7: U1.M3 (SA7), U2.R2 (A7), U3.R2 (A7)
SA8: U1.AA3 (SA8), U2.T8 (A8), U3.T8 (A8)
SA9: U1.P4 (SA9), U2.R3 (A9), U3.R3 (A9)
SA10: U1.L3 (SA10), U2.L7 (A10/AP), U3.L7 (A10/AP)
SA11: U1.W3 (SA11), U2.R7 (A11), U3.R7 (A11)
SA12: U1.P3 (SA12), U2.N7 (A12/#BC), U3.N7 (A12/#BC)
SA13: U1.Y3 (SA13), U2.T3 (A13), U3.T3 (A13)
SA14: U1.R3 (SA14), U2.T7 (NC/A14), U3.T7 (NC/A14)
SA15: U1.AA4 (SCS1), U2.M7 (NC), U3.M7 (NC)
SCK: R9.2, U1.V1 (SCK)
SCK#: R10.2, U1.V2 (SCK#/SCKB)
SCS0: U1.V3 (SCS0/SCS), U2.L2 (#CS), U3.L2 (#CS)
SD0-CLK: R11.2, U1.L20 (SDC0_CLK/UART0_TX/PF2)
SD0-CLKIN: R11.1, SD/MMC.5 (CLK/SCLK)
SD0-CMD: R2.1, SD/MMC.3 (CMD/DI), U1.L19 (SDC0_CMD/JTAG_DO1/PF3)
SD0-D0: R3.1, SD/MMC.7 (DAT0/DO), U1.M19 (SDC0_D0/JTAG_DI1/PF1)
SD0-D1: R5.1, SD/MMC.8 (DAT1/RES), U1.M20 (SDC0_D1/JTAG_MS1/PF0)
SD0-D2: R6.1, SD/MMC.1 (DAT2/RES), U1.K19 (SDC0_D2/JTAG_CK1/PF5)
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
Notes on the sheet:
POWER SUPPLY CIRCUIT
LI-ION_BATTERY
2 x [4Gb DDR3 SDRAM (256Mx16)]
MicroSD
Joystick
USB-HOSTs
HDMI
Touch pad
ADC
We have used a number of fully compatible
but different DDR3 memories due to supply unavailability.
In such cases the memory part name
in the schematic might remain outdated.
It is recommended to always refer to the
exact memory name printed on the component itself.
TVin can be connected to GND if not used
Ethernet
EEPROM
MAC Address
16 Kbit
(2048x8)
I2C Address: 0xA0
ToDo: Ferrite (select w/high Z at high F, low Z at low F). Try to block everything >1MHz or so.
C3: Use 1uF to filter high frequency noise, or 10uF if lower frequency noise is present
NOTE: For the best power on/off pop performance, the amplifier should be set in the shutdown mode prior to power on/off operation (set SD low to power down the amp).
Audio
2*100nf removed as they're somewhere else
WIFI/BT
LED
SATA
Impedance control 100ohm
Extensions
eMMC
LCD
